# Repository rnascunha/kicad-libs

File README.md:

# kicad-libs
Kicad libs with spice models, 3Ds and others

Directories:
* `libs` - spice models, datasheets, 3D step files...
* `examples` - examples/reference circuits, simulations...

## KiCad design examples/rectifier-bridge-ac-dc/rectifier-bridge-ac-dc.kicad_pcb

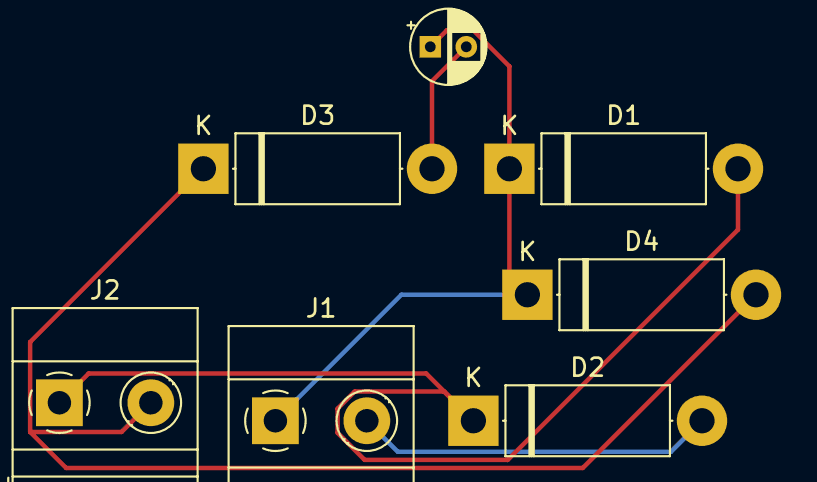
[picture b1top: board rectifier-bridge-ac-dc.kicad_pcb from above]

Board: 2 copper layers, 7 parts (0 on the bottom side), 4 nets.

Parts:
C1: 10uF; CP_Radial_D4.0mm_P2.00mm
D1, D2, D3, D4: D; D_5W_P12.70mm_Horizontal
J1, J2: Conn_01x02; TerminalBlock_Phoenix_MKDS-1,5-2-5.08_1x02_P5.08mm_Horizont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

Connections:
/Rectifier: C1.1, D1.1 (K), D4.1 (K), J1.1
/VCC: D1.2 (A), D2.1 (K), J2.1
GND: D3.1 (K), D4.2 (A), J2.2
GND1: C1.2, D2.2 (A), D3.2 (A), J1.2

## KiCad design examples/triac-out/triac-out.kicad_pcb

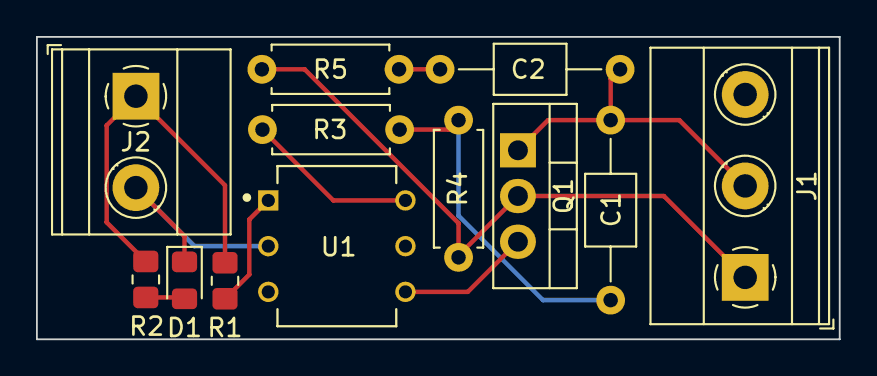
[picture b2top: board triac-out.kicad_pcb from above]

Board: 2 copper layers, 44.6 x 16.8 mm, 12 parts (0 on the bottom side), 10 nets.

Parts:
C1: 0nF; C_Axial_L3.8mm_D2.6mm_P10.00mm_Horizontal
C2: 10nF; C_Axial_L3.8mm_D2.6mm_P10.00mm_Horizontal
D1: LED; LED_0805_2012Metric_Pad1.15x1.40mm_HandSolder
J1: Power; TerminalBlock_Phoenix_MKDS-1,5-3-5.08_1x03_P5.08mm_Horizont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
J2: DC_in; TerminalBlock_Phoenix_MKDS-1,5-2-5.08_1x02_P5.08mm_Horizont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
Q1: Triac; TO-220-3_Vertical
R1: 170; R_0805_2012Metric_Pad1.20x1.40mm_HandSolder
R2: 330; R_0805_2012Metric_Pad1.20x1.40mm_HandSolder
R3: 330; R_Axial_DIN0207_L6.3mm_D2.5mm_P7.62mm_Horizontal
R4: 470; R_Axial_DIN0207_L6.3mm_D2.5mm_P7.62mm_Horizontal
R5: 39; R_Axial_DIN0207_L6.3mm_D2.5mm_P7.62mm_Horizontal
U1: MOC3021M; DIP762W45P254L889H508Q6

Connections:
/Load: C1.2, C2.2, J1.2, Q1.1 (A1)
/Phase: J1.1, Q1.2 (A2), R4.2, R5.2
/Vin: J2.1, R1.1, R2.1
/gate: Q1.3 (G), U1.4
GND1: D1.1 (K), J2.2, U1.2
unnamed: C1.1, R3.2, R4.1
unnamed: C2.1, R5.1
unnamed: D1.2 (A), R2.2
unnamed: R1.2, U1.1
unnamed: R3.1, U1.6

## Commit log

2023-11-01 First commit.
2023-11-08 Updated moc3021 footprint.
2023-11-23 Added examples.
